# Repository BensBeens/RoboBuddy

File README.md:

# RoboBuddy
Robo companion using RP2040 and other modules.
The plan is to have a robot that is able to change states/faces by reading the accelerometer data. It will have a variety of faces and sounds.
I am first testing the idea on a Raspberry Pi Pico with external modules. Once I finish the prototype I will make the design smaller by making my own PCB with the RP2040.
The software I am using is Thonny for the micropython code and KiCad for the PCB and schematic design.
8/15/2024: I have finished testing it on the pico and have been working on a schematic for the past weeks. I just finished the pcb design and generated the gerber files. I will hopefully begin production soon and see if my pcb works. I will be using JLCPCB.com to make the pcb board.
8/27/2024: Turns out there is an issue with my PCB's Flash memory (it is able to load as an external USB but doesn't load any UF2 files I put in it). I will downscale the project to just be a shield that will connect to a pico. The latest file should be uploaded in the "RoboBuddy Folder" and files named "RoboBuddy.kicad_..."

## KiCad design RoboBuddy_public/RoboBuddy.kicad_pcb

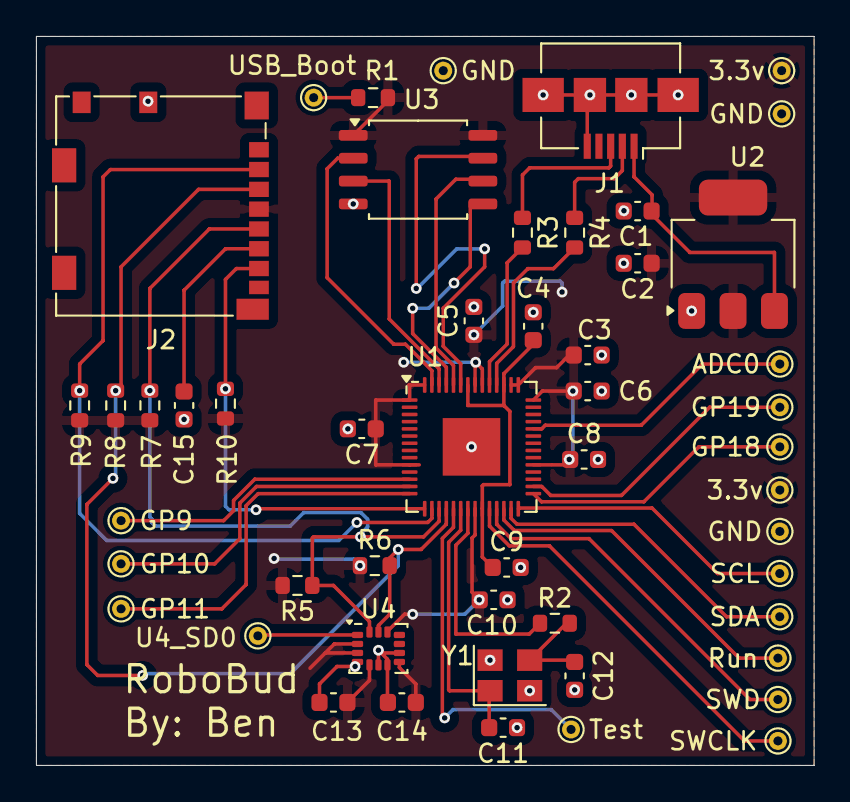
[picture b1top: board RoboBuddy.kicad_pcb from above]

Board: 2 copper layers, 43.2 x 40.5 mm, 51 parts (0 on the bottom side), 35 nets.

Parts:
3.3v, 3.3v#2: TestPoint_THTPad_D1.0mm_Drill0.5mm
ADC0: TestPoint_THTPad_D1.0mm_Drill0.5mm
C1, C2: 10u; C_0603_1608Metric
C3, C4: 1u; C_0603_1608Metric
C5, C6, C7, C8, C9, C10, C13, C14, C15: 100n; C_0603_1608Metric
C11, C12: 15p; C_0603_1608Metric
GND: TestPoint_THTPad_D1.0mm_Drill0.5mm
GND#2, GND#3: TestPoint_THTPad_D1.0mm_Drill0.5mm
GP9, GP10, GP11, GP18, GP19: TestPoint_THTPad_D1.0mm_Drill0.5mm
J1: USB_B_Micro; USB_Micro-B_Amphenol_10104110_Horizontal
J2: Micro_SD_Card; microSD_HC_Molex_104031-0811
R1, R2: 1k; R_0603_1608Metric
R3, R4: 27.4; R_0603_1608Metric
R5, R6, R7, R8, R9, R10: 10k; R_0603_1608Metric
Run: TestPoint_THTPad_D1.0mm_Drill0.5mm
SCL: TestPoint_THTPad_D1.0mm_Drill0.5mm
SDA: TestPoint_THTPad_D1.0mm_Drill0.5mm
SWCLK: TestPoint_THTPad_D1.0mm_Drill0.5mm
SWD: TestPoint_THTPad_D1.0mm_Drill0.5mm
Test: TestPoint_THTPad_D1.0mm_Drill0.5mm
U1: RP2040; QFN-56-1EP_7x7mm_P0.4mm_EP3.2x3.2mm
U2: NCP1117-3.3_SOT223; SOT-223-3_TabPin2
U3: W25Q128JVS; SOIC-8_5.23x5.23mm_P1.27mm
U4: LSM6DS3; LGA-14_3x2.5mm_P0.5mm_LayoutBorder3x4y
U4_SD0: TestPoint_THTPad_D1.0mm_Drill0.5mm
USB_Boot: TestPoint_THTPad_D1.0mm_Drill0.5mm
Y1: ABM8-272-T3; Crystal_SMD_3225-4Pin_3.2x2.5mm

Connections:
+1V1: C4.1, C9.1, U1.23 (DVDD), U1.45 (VREG_VOUT), U1.50 (DVDD)
+3.3V: 3.3v.1, 3.3v#2.1, C2.1, C3.1, C5.1, C6.1, C7.1, C8.1, C10.1, C13.2, C14.1, J2.4 (VDD), R1.2, R5.2, R6.1, R7.2, R8.2, R9.2, R10.2, U1.1 (IOVDD), U1.10 (IOVDD), U1.22 (IOVDD), U1.33 (IOVDD), U1.42 (IOVDD), U1.43 (ADC_AVDD), U1.44 (VREG_IN), U1.48 (USB_VDD), U1.49 (IOVDD), U1.56 (QSPI_SS), U2.2 (VO), U3.1 (~CS), U3.8 (VCC), U4.2 (SDX), U4.3 (SCX), U4.5 (VDDIO), U4.8 (VDD), U4.12 (CS)
/CS_SD: J2.2 (DAT3/CD), R9.1, U1.16 (GPIO13)
/GPIO_9: GP9.1, U1.12 (GPIO9)
/GPIO_10: GP10.1, U1.13 (GPIO10)
/GPIO_18: GP18.1, U1.29 (GPIO18)
/GPIO_19: GP19.1, U1.30 (GPIO19)
/GPIO_26_ADC0: ADC0.1, U1.38 (GPIO26_ADC0)
/MISO_SD: J2.7 (DAT0), R10.1, U1.15 (GPIO12)
/Pad: R1.1, USB_Boot.1
/QSPI_SCLK: U1.52 (QSPI_SCLK), U3.6 (CLK)
/QSPI_SD0: U1.53 (QSPI_SD0), U3.5 (DI(IO0))
/QSPI_SD1: U1.55 (QSPI_SD1), U3.2 (DO(IO1))
/QSPI_SD2: U1.54 (QSPI_SD2), U3.3 (IO2)
/QSPI_SD3: U1.51 (QSPI_SD3), U3.7 (IO3)
/RUN: Run.1, U1.26 (RUN)
/SCL_GRYO/MOSI_SD: J2.3 (CMD), R6.2, R8.1, U1.18 (GPIO15), U4.13 (SCL)
/SCL_OLED: SCL.1, U1.28 (GPIO17)
/SD0_Pad: U4.1 (SDO/SA0), U4_SD0.1
/SDA_GYRO/SCK_SD: J2.5 (CLK), R5.1, R7.1, U1.17 (GPIO14), U4.14 (SDA)
/SDA_OLED: SDA.1, U1.27 (GPIO16)
/SWCLK: SWCLK.1, U1.24 (SWCLK)
/SWD: SWD.1, U1.25 (SWD)
/TESTEN: Test.1, U1.19 (TESTEN)
/USB_D+: J1.3 (D+), R3.1
/USB_D-: J1.2 (D-), R4.1
/XIN: C11.2, U1.20 (XIN), Y1.1
/XOUT: R2.2, U1.21 (XOUT)
/speaker: GP11.1, U1.14 (GPIO11)
GND: C1.2, C2.2, C3.2, C4.2, C5.2, C6.2, C7.2, C8.2, C9.2, C10.2, C11.1, C12.1, C13.1, C14.2, C15.1, GND.1, GND#2.1, GND#3.1, J1.5 (GND), J1.6 (Shield), J2.9 (SHIELD), U1.57 (GND), U2.1 (GND), U3.4 (GND), U4.4 (INT1), U4.6 (GND), U4.7 (GND), U4.9 (INT2), Y1.2, Y1.4
unnamed: C12.2, R2.1, Y1.3
unnamed: C15.2, J2.6 (VSS)
unnamed: R4.2, U1.46 (USB_DM)
unnamed: R3.2, U1.47 (USB_DP)
VBUS: C1.1, J1.1 (VBUS), U2.3 (VI)

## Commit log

2024-08-02 First upload
    Set up the schematic for the PCB design. RP2040 and external modules are on the schematic. Planning on adding through-hole solder points to attach the external modules to the PCB. (unless I figure ou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
2024-08-02 First upload of the Thonny code
    Micropython code for Raspberry Pi Pico. I used this code to test on a Pico before ordering my PCB.
2024-08-13 Add files via upload
    Changes:
    - looked at kicad and jlcpcb.com to select some IC to put on my PCB
    - added SD card and gyro/accelerometer IC to PCB schematic
2024-08-13 Add files via upload
    Roughly added the connections and necessary components for Micro SD card reader and Accelerometer/Gyro modules to the RP2040
    - added pullup resistors
    - added decoupling capacitors
2024-08-15 Add files via upload
    Finalized the schematic and started on the pcb design
2024-08-16 Add files via upload
    Finished the connecting everything on the pcb schematic. I will now get rid of some of the overlapping silkscreen (mainly getting rid of the capacitors and resistors tags)
2024-08-16 Add files via upload
    Finished removing the unwanted silkscreen and added some additional silkscreen text. Then I generated the gerber files.
2024-08-16 Add files via upload
    Finalized PCB schematic and sent it to JLCPCB to be manufactured
2024-08-16 Delete
2024-08-16 Add files via upload
    did some file cleanup
2024-08-16 Add files via upload
    added pictures
2024-08-16 Update README.md
    added pictures to the readme
